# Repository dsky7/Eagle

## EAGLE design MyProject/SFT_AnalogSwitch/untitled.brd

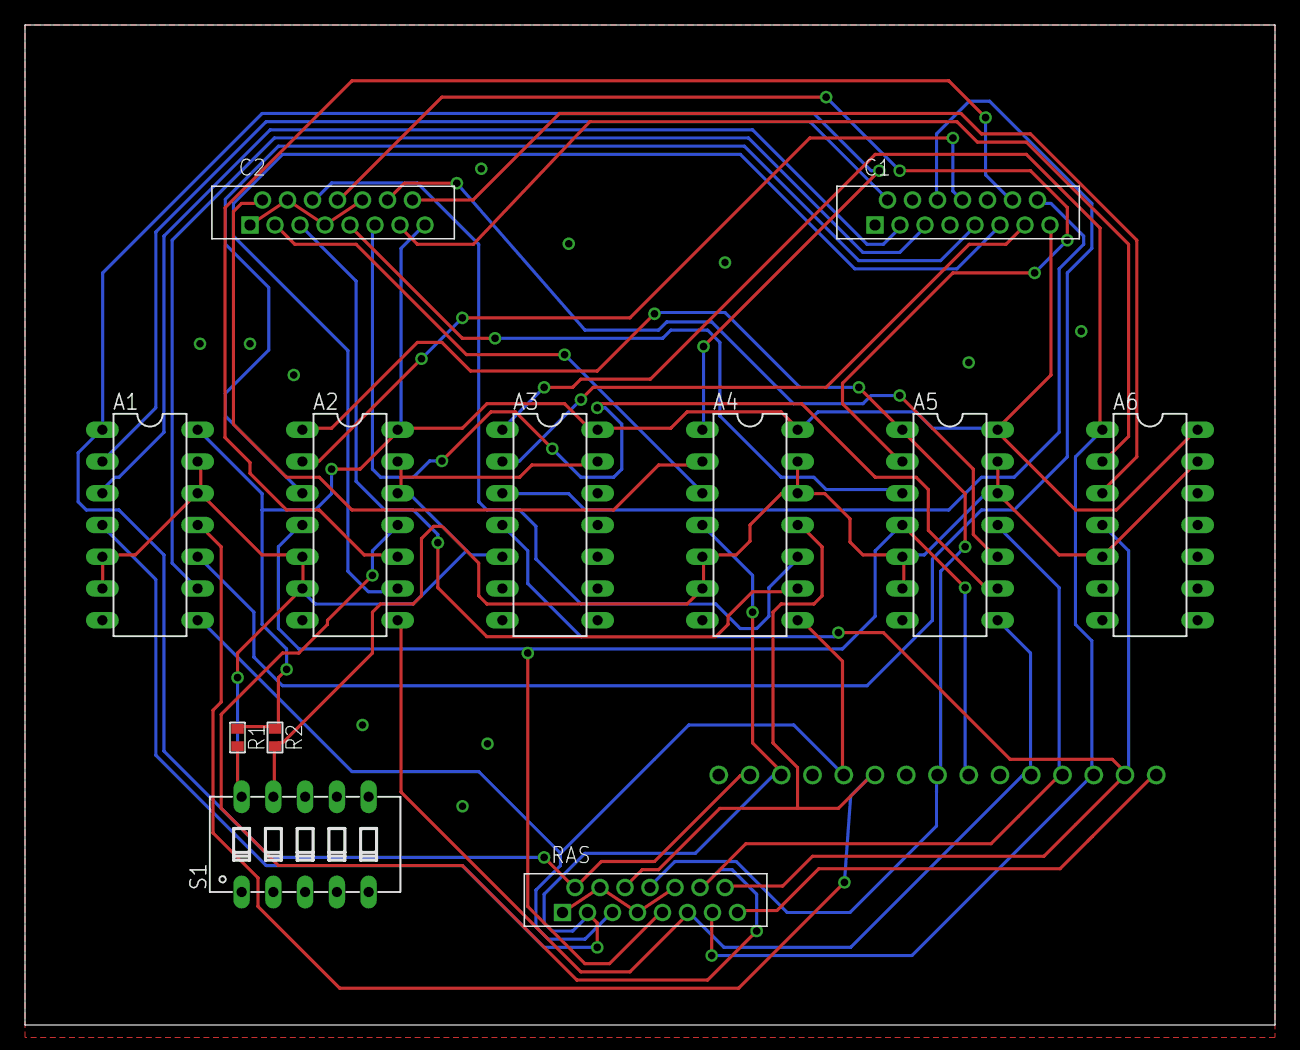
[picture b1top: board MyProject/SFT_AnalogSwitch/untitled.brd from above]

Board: 2 copper layers, 100.0 x 80.0 mm, 27 parts (0 on the bottom side), 35 nets.

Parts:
A1, A2, A3, A4, A5, A6: SN74HC4066; DIL14
C1, C2: FMZ15
R1, R2: 1608
RAS: FMZ15
S1: DIP05YL
U$4, U$5, U$6, U$7, U$8, U$9, U$10, U$11, U$12, U$13, U$14, U$15, U$16, U$17, U$18: CHECK_0.8MM

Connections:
2: A1.1, A4.1, RAS.2, U$5.P$1
3: A1.4, A4.4, RAS.3, U$6.P$1
5: A1.8, A4.8, RAS.5, U$8.P$1
6: A1.11, A4.11, RAS.6, U$9.P$1
8: A2.1, A5.1, RAS.8, U$11.P$1
9: A2.4, A5.4, RAS.9, U$12.P$1
11: A2.8, A5.8, RAS.11, U$14.P$1
12: A2.11, A5.11, RAS.12, U$15.P$1
13: A3.1, A6.1, RAS.13, U$16.P$1
14: A3.4, A6.4, RAS.14, U$17.P$1
15: RAS.15, U$18.P$1
+3.3V: A1.14, A2.14, A3.14, A4.14, A5.14, A6.14, C1.15, C2.15, R1.2, R2.2
GND: A1.7, A2.7, A3.7, A4.7, A5.7, A6.7, C1.1, C1.4, C1.7, C1.10, C2.1, C2.4, C2.7, C2.10, RAS.1, RAS.4, RAS.7, RAS.10, S1.1, S1.2, U$4.P$1, U$7.P$1, U$10.P$1, U$13.P$1
unnamed: A4.2, C2.2
unnamed: A4.3, C2.3
unnamed: A4.9, C2.5
unnamed: A5.3, C2.9
unnamed: A5.2, C2.8
unnamed: A4.10, C2.6
unnamed: A1.2, C1.2
unnamed: A1.3, C1.3
unnamed: A6.3, C2.14
unnamed: A1.9, C1.5
unnamed: A6.2, C2.13
unnamed: A5.10, C2.12
unnamed: A5.9, C2.11
unnamed: A2.3, C1.9
unnamed: A2.2, C1.8
unnamed: A1.10, C1.6
unnamed: A3.3, C1.14
unnamed: A3.2, C1.13
unnamed: A2.10, C1.12
unnamed: A2.9, C1.11
SIGA: A1.5, A1.6, A1.12, A1.13, A2.5, A2.6, A2.12, A2.13, A3.5, A3.13, R1.1, S1.10
SIGB: A4.5, A4.6, A4.12, A4.13, A5.5, A5.6, A5.12, A5.13, A6.5, A6.13, R2.1, S1.9

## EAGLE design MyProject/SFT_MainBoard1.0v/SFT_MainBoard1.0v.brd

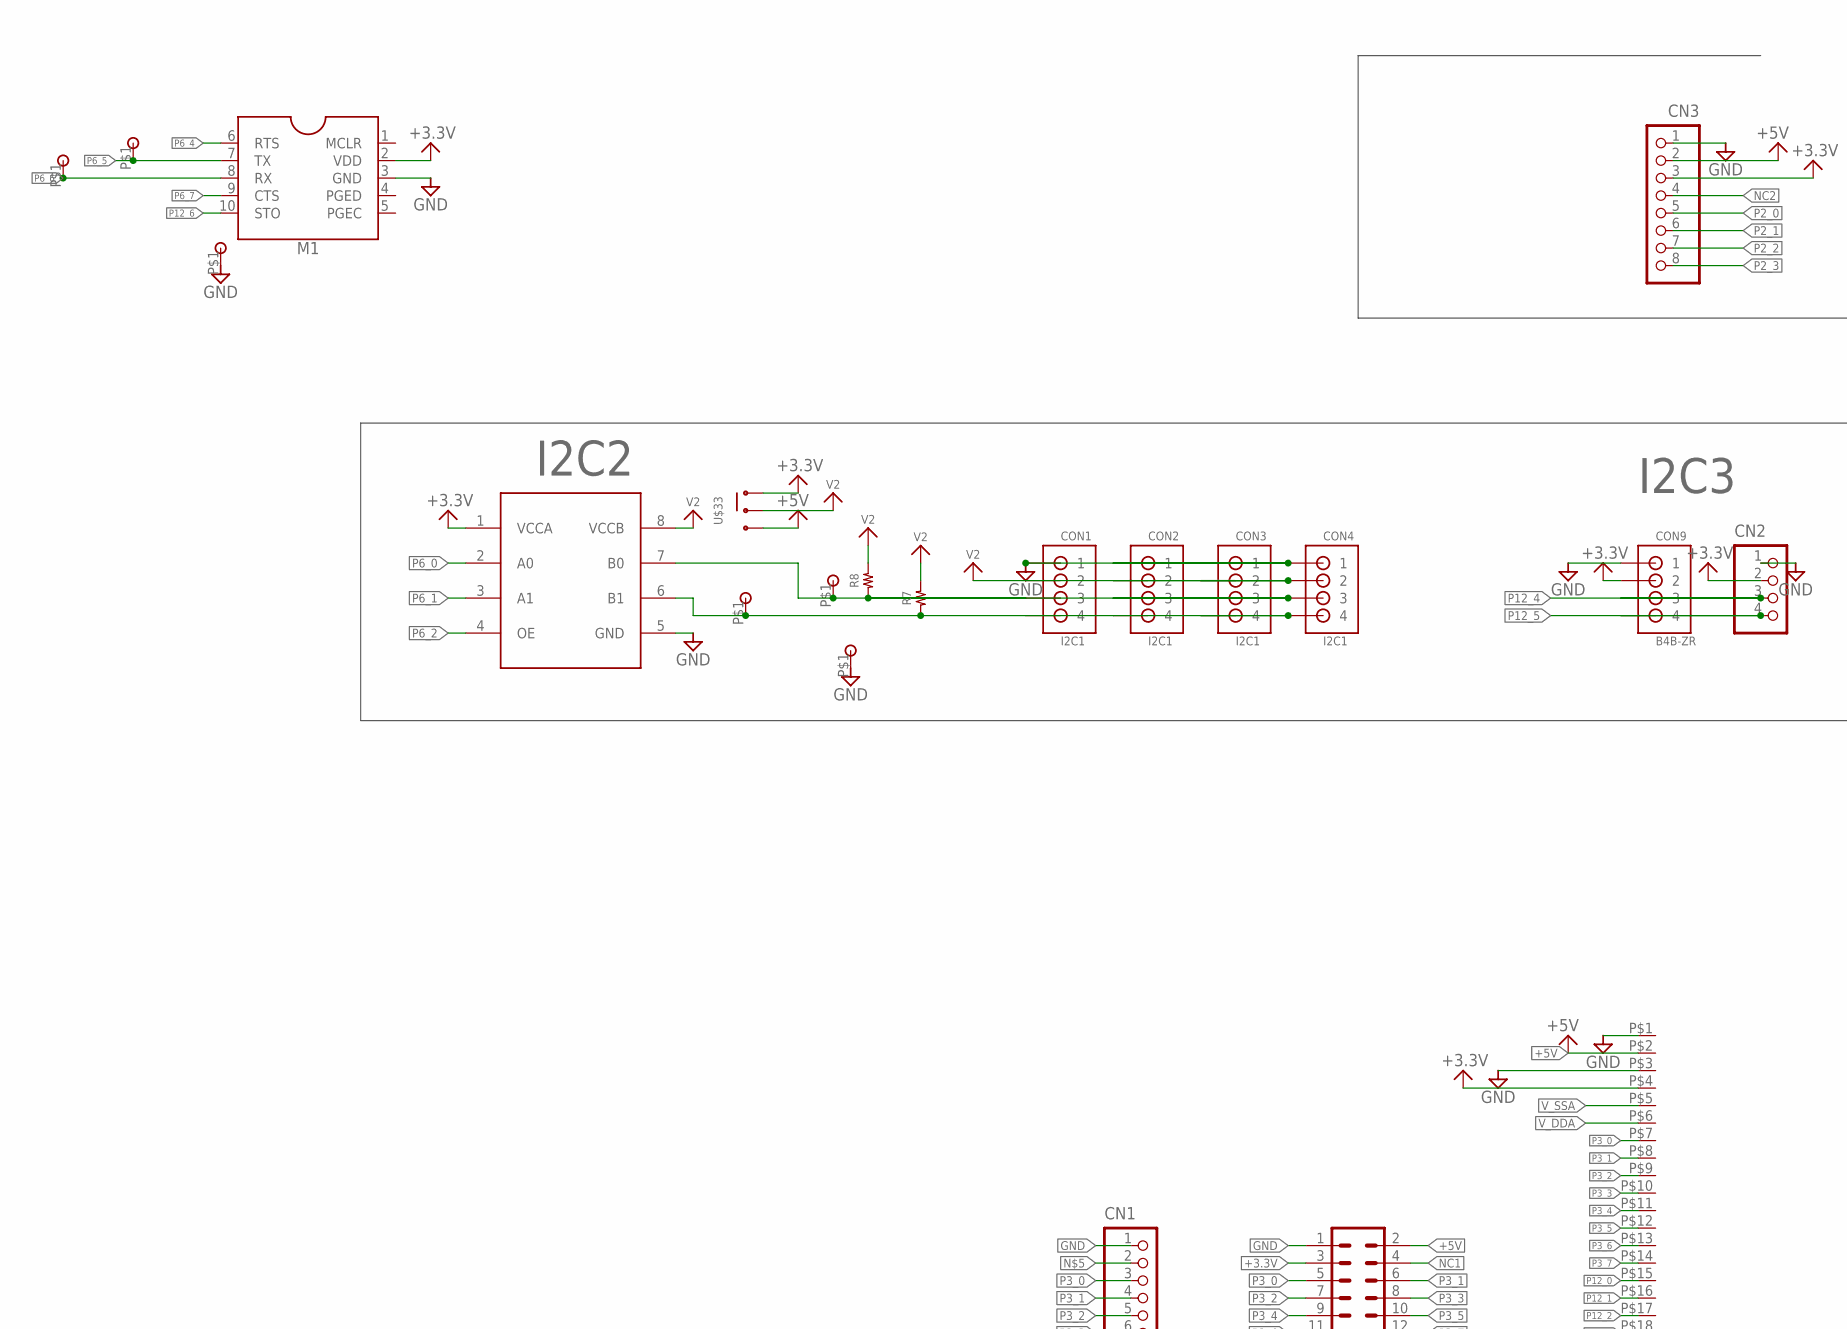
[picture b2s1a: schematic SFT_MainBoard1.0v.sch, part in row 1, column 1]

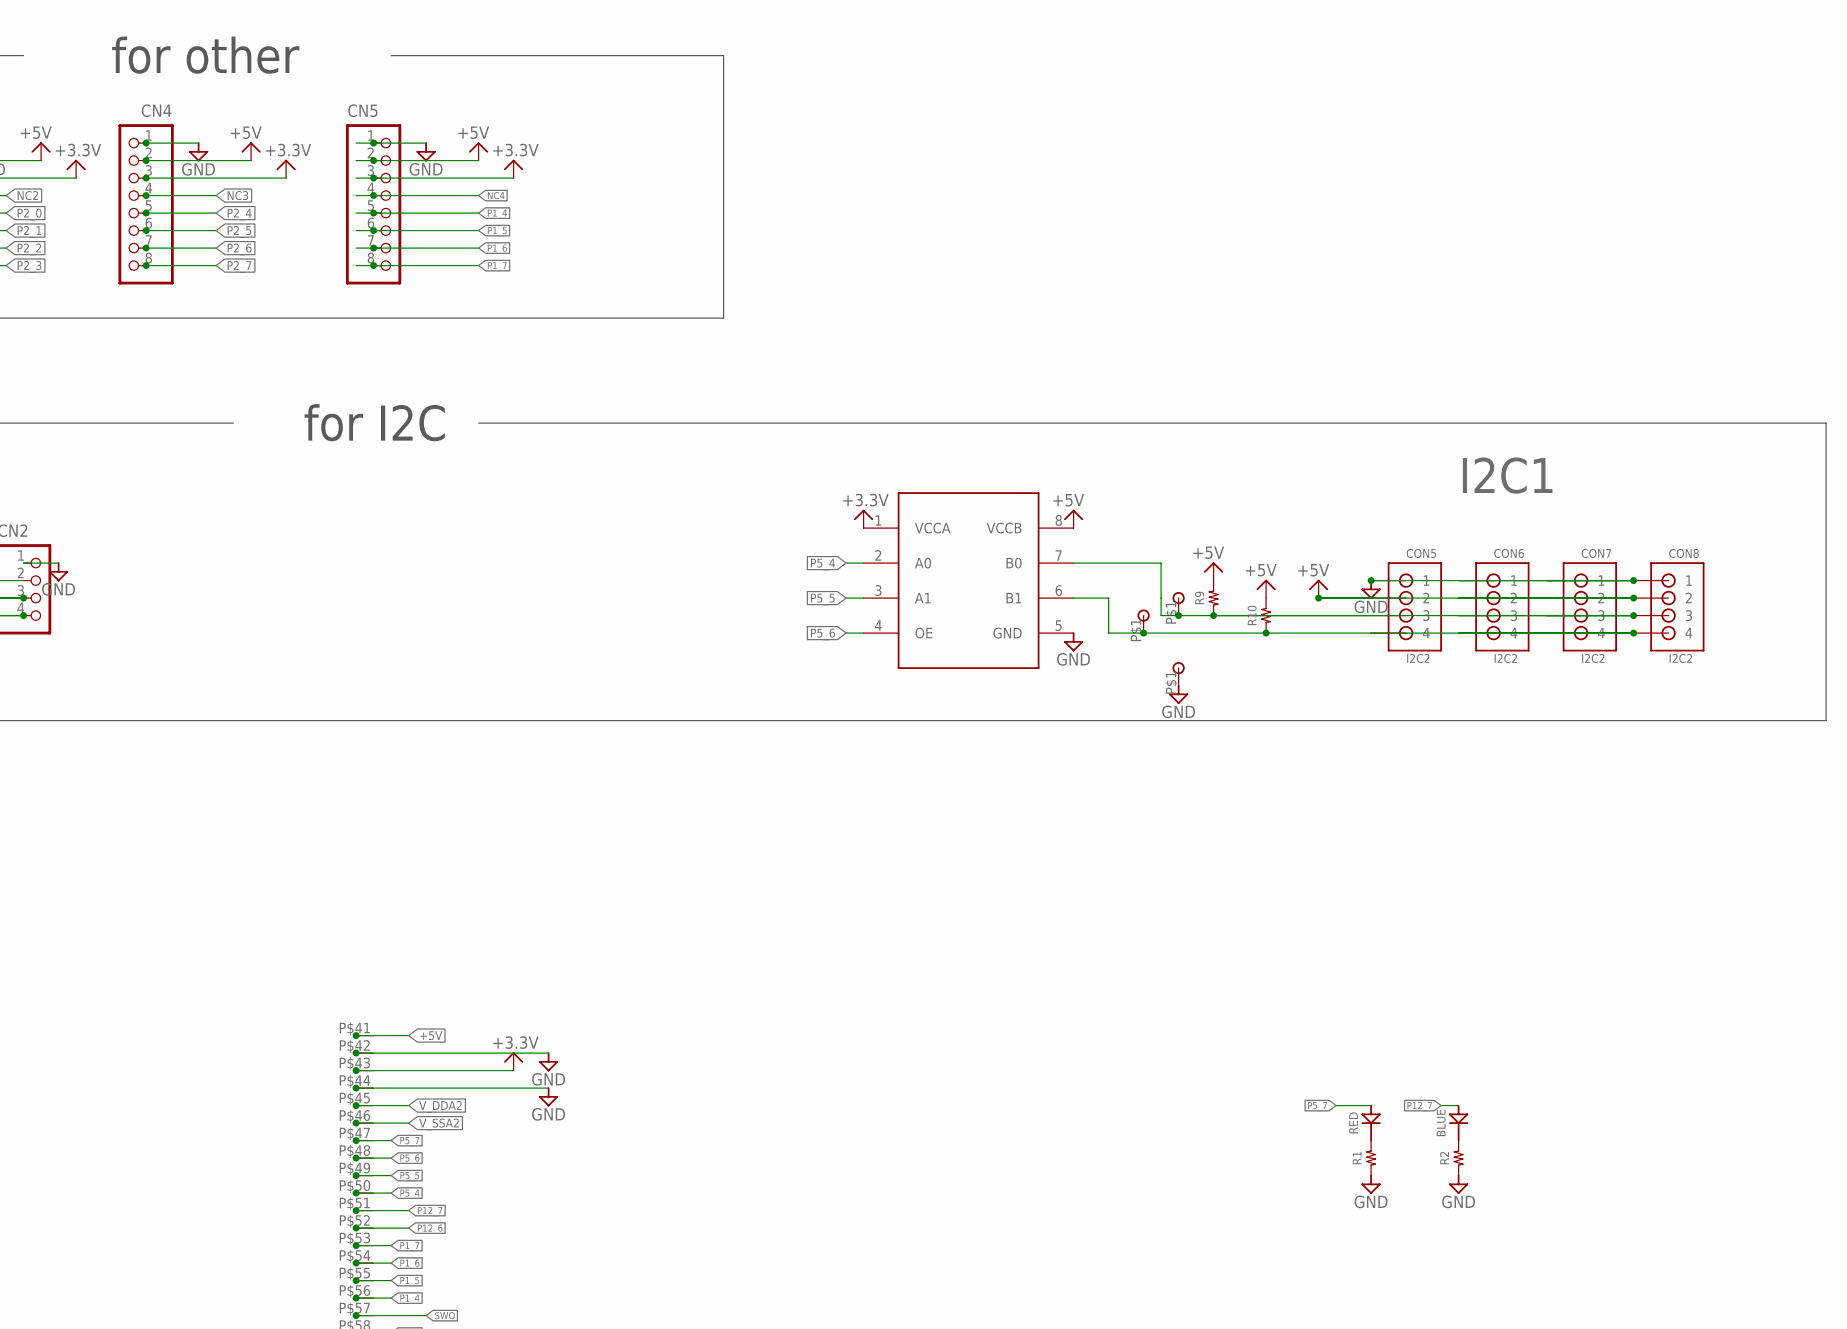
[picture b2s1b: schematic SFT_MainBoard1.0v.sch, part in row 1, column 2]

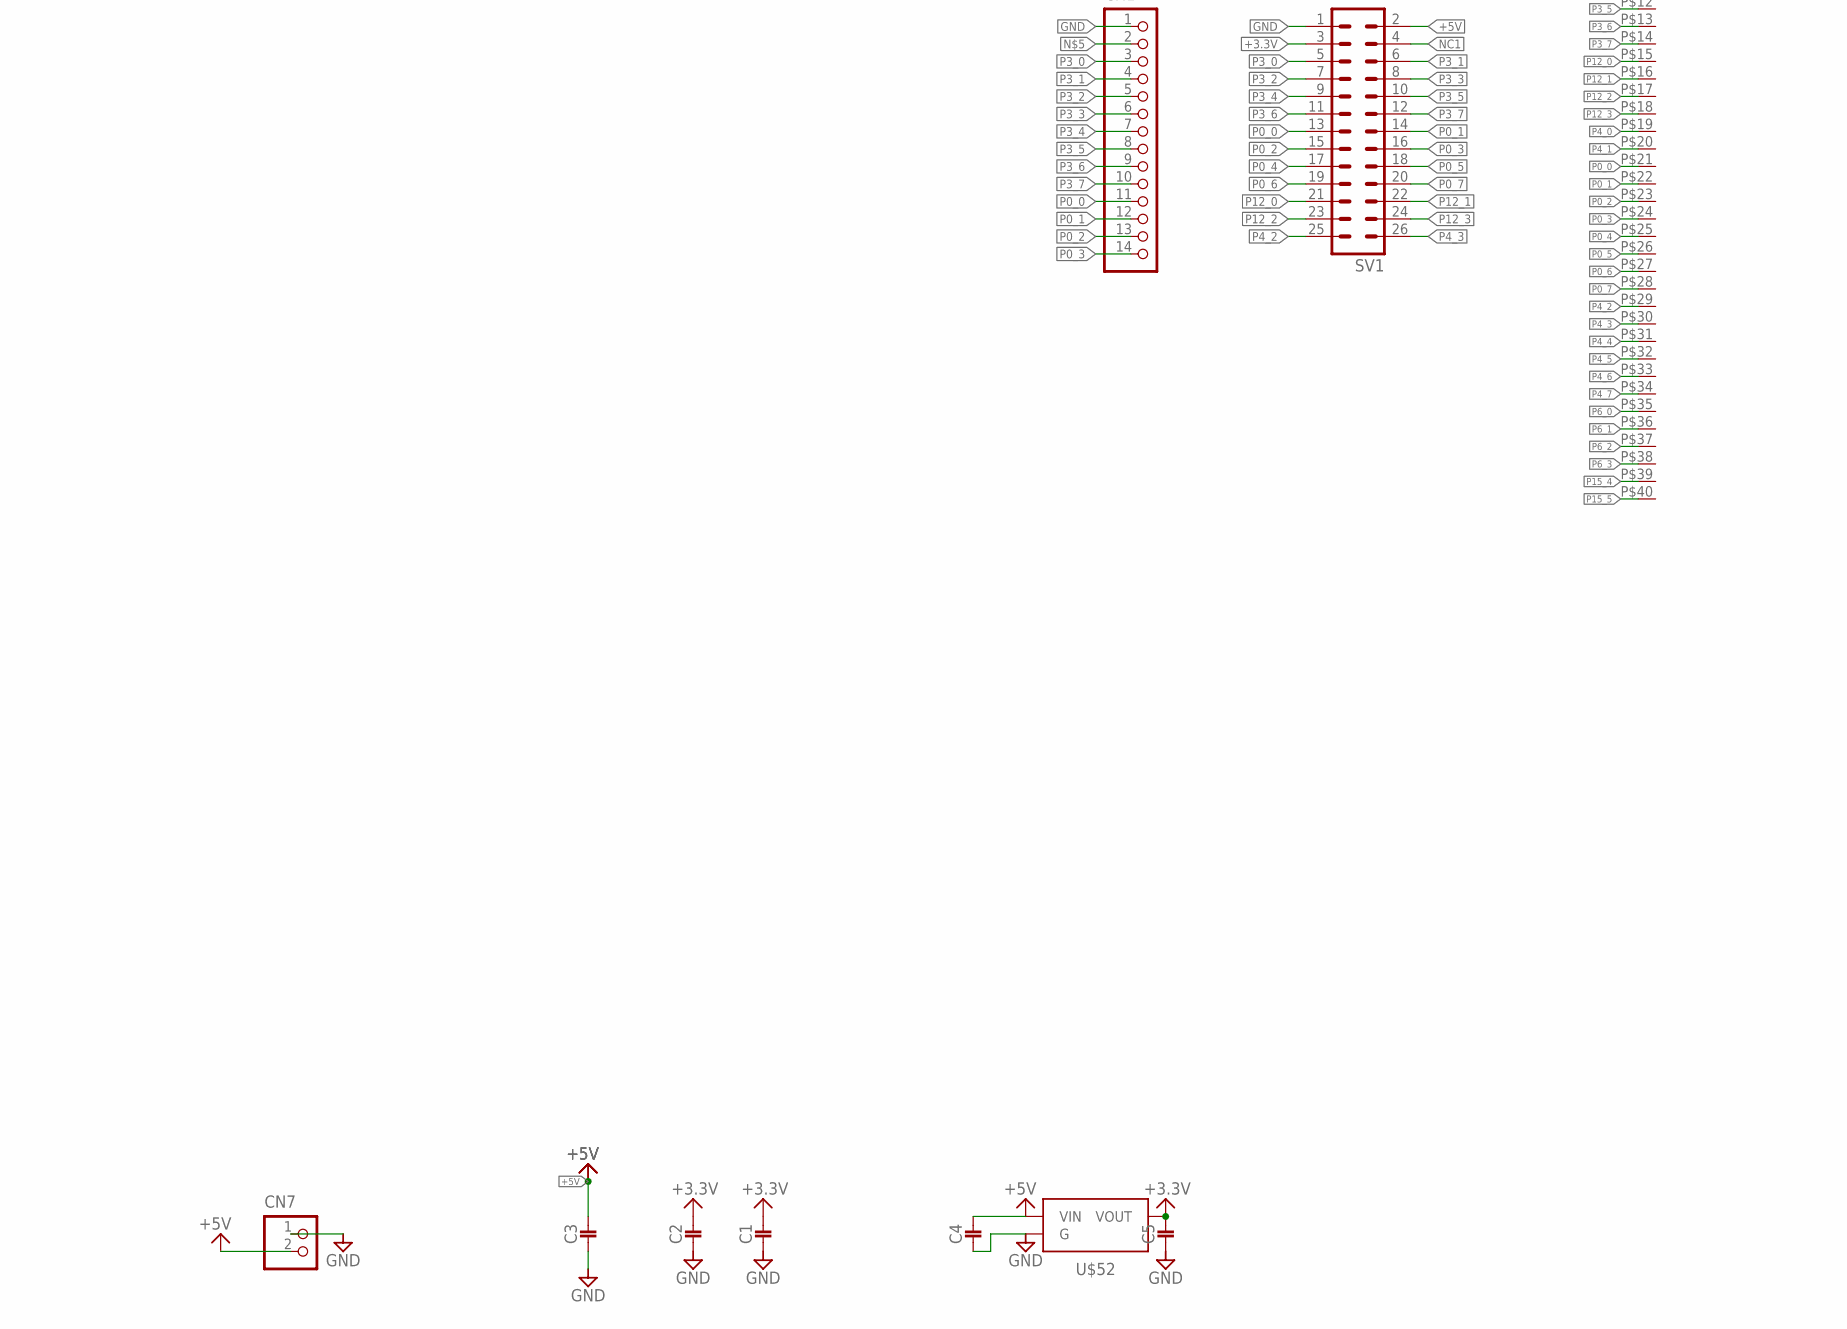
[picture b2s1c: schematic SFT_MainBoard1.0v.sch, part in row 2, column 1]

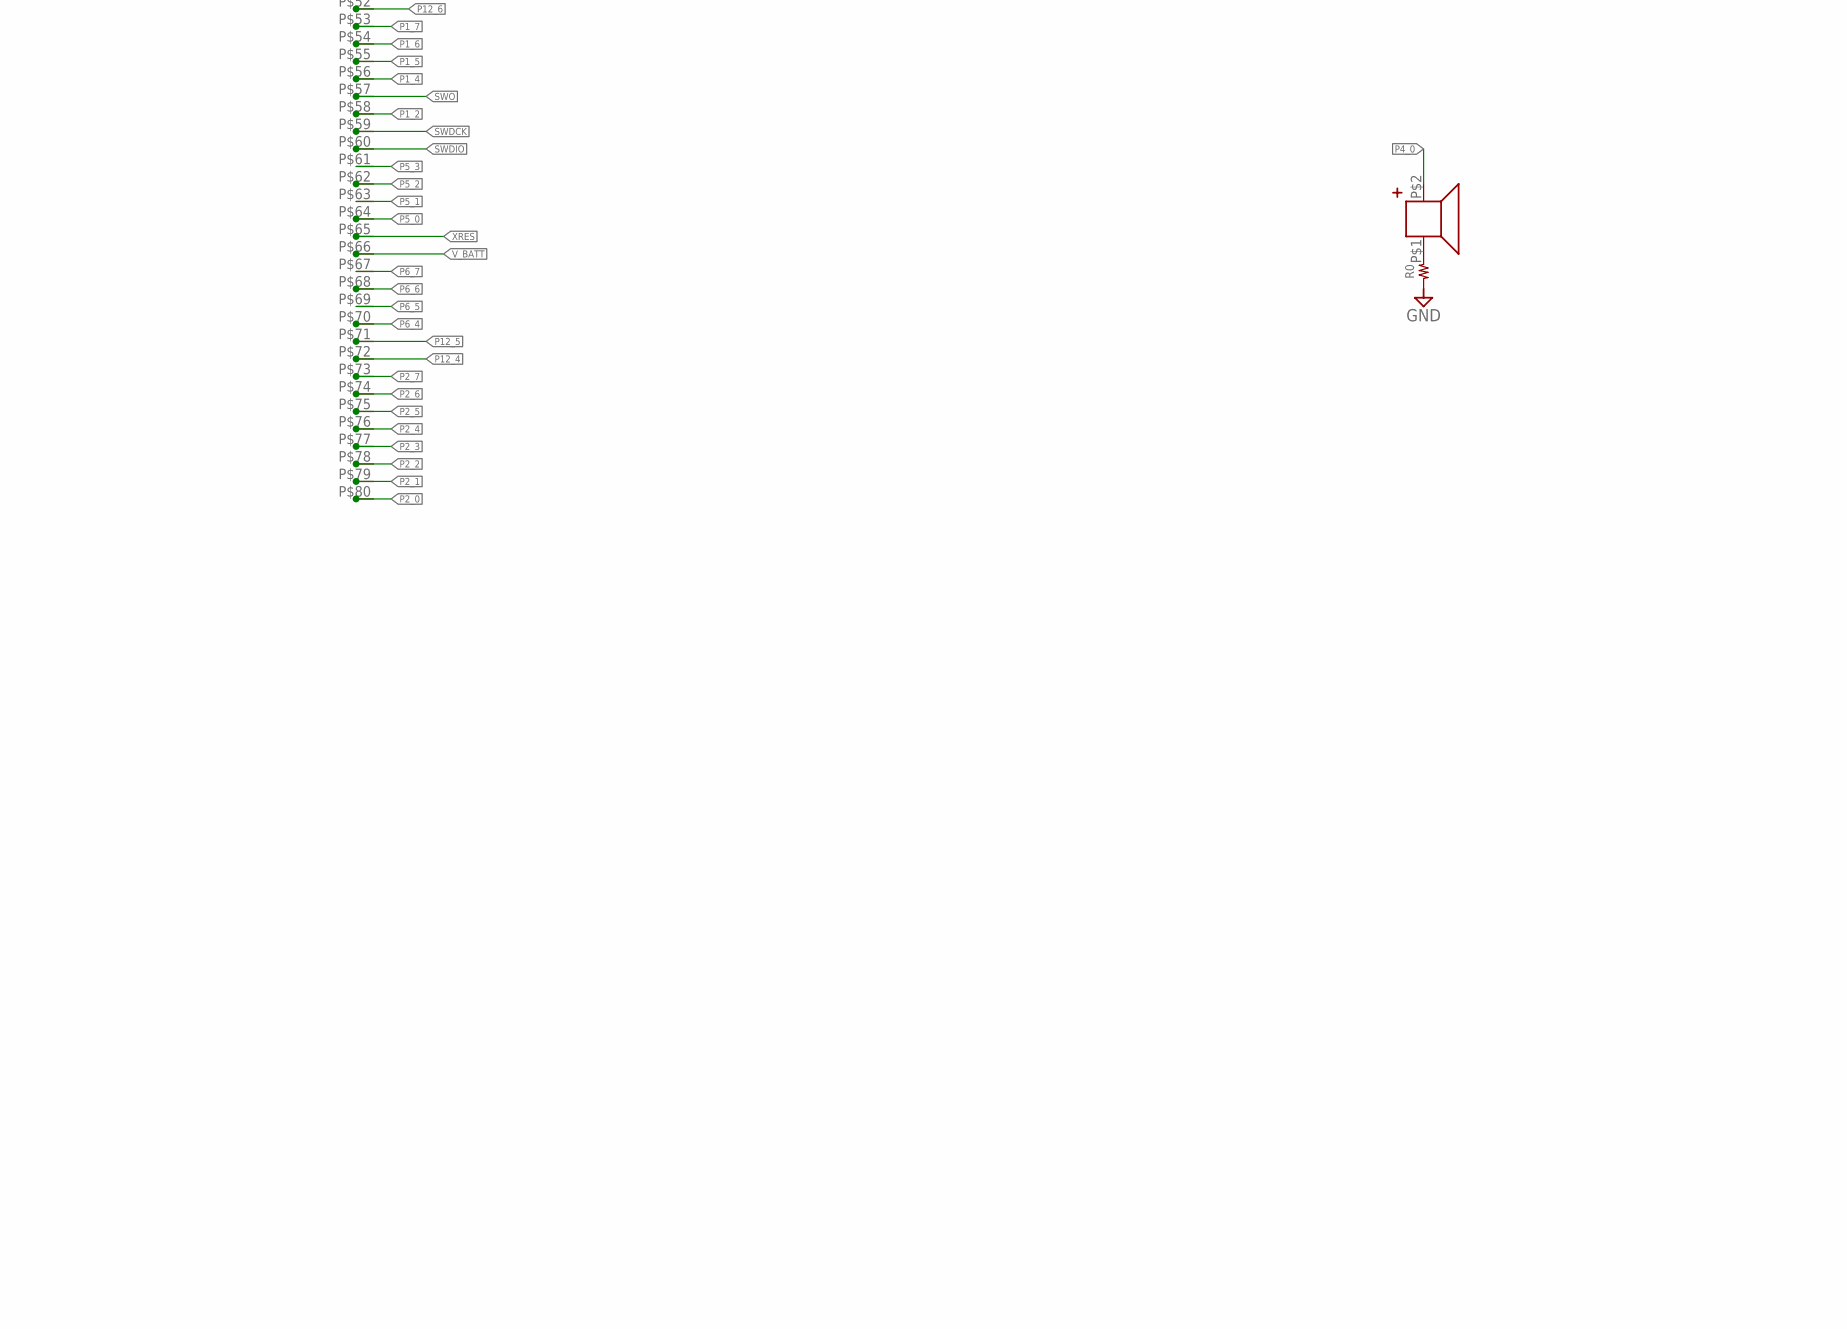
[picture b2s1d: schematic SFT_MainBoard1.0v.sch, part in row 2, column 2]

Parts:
BLUE: CHIPLED; 1608
C1, C2, C3, C4, C5: 1608
CN1: B14B-XASK-1
CN2: B4B-PH-K-S
CN3, CN4, CN5: B8B-PH-K-S
CN7: B2B-PH-K-S
CON1, CON2, CON3, CON4: I2C1; B4B-ZR
CON5, CON6, CON7, CON8: I2C2; B4B-ZR
CON9: B4B-ZR
IC1, IC2: I2C_FXMA2102; DIL08
M1: SBDBT; DIL10
R0, R1, R2, R7, R8, R9, R10: RESISTOR__SMD; 1608
RED: CHIPLED; 1608
SP: PKLCS1212E4001
SV1: ML26
U$2: PSOC_5LP
U$15, U$18, U$37, U$38, U$39, U$78, U$79, U$82, U$83: CHECK_0.8MM
U$33: SS12D01G4
U$52: NJM2845; TO252

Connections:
+3.3V: C1.P$1 (1), C2.P$1 (1), C5.P$1 (1), CN2.2, CN3.3, CN4.3, CN5.3, CON9.2, IC1.1 (VCCA), IC2.1 (VCCA), M1.2 (VDD), SV1.3, U$2.P$4, U$2.P$43, U$33.1, U$52.3 (VOUT)
+5V: C3.P$1 (1), C4.P$1 (1), CN3.2, CN4.2, CN5.2, CN7.2, CON5.2, CON6.2, CON7.2, CON8.2, IC1.8 (VCCB), R9.2, R10.2, SV1.2, U$2.P$2, U$2.P$41, U$33.3, U$52.1 (VIN)
GND: C1.P$2 (2), C2.P$2 (2), C3.P$2 (2), C4.P$2 (2), C5.P$2 (2), CN1.1, CN2.1, CN3.1, CN4.1, CN5.1, CN7.1, CON1.1, CON2.1, CON3.1, CON4.1, CON5.1, CON6.1, CON7.1, CON8.1, CON9.1, IC1.5 (GND), IC2.5 (GND), M1.3 (GND), R0.1, R1.1, R2.1, SV1.1, U$2.P$1, U$2.P$3, U$2.P$42, U$2.P$44, U$37.P$1, U$38.P$1, U$39.P$1, U$52.2 (G)
unnamed: R0.2, SP.P$1 (MINUS)
unnamed: R1.2, RED.2 (K)
unnamed: BLUE.2 (K), R2.2
unnamed: CON1.3, CON2.3, CON3.3, CON4.3, IC2.7 (B0), R8.1, U$79.P$1
unnamed: CON1.4, CON2.4, CON3.4, CON4.4, IC2.6 (B1), R7.1, U$78.P$1
unnamed: CON5.3, CON6.3, CON7.3, CON8.3, IC1.7 (B0), R9.1, U$18.P$1
unnamed: CON5.4, CON6.4, CON7.4, CON8.4, IC1.6 (B1), R10.1, U$15.P$1
NC1: SV1.4
NC2: CN3.4
NC3: CN4.4
NC4: CN5.4
P0_0: CN1.11, SV1.13, U$2.P$21
P0_1: CN1.12, SV1.14, U$2.P$22
P0_2: CN1.13, SV1.15, U$2.P$23
P0_3: CN1.14, SV1.16, U$2.P$24
P0_4: SV1.17, U$2.P$25
P0_5: SV1.18, U$2.P$26
P0_6: SV1.19, U$2.P$27
P0_7: SV1.20, U$2.P$28
P1_2: U$2.P$58
P1_4: CN5.5, U$2.P$56
P1_5: CN5.6, U$2.P$55
P1_6: CN5.7, U$2.P$54
P1_7: CN5.8, U$2.P$53
P2_0: CN3.5, U$2.P$80
P2_1: CN3.6, U$2.P$79
P2_2: CN3.7, U$2.P$78
P2_3: CN3.8, U$2.P$77
P2_4: CN4.5, U$2.P$76
P2_5: CN4.6, U$2.P$75
P2_6: CN4.7, U$2.P$74
P2_7: CN4.8, U$2.P$73
P3_0: CN1.3, SV1.5, U$2.P$7
P3_1: CN1.4, SV1.6, U$2.P$8
P3_2: CN1.5, SV1.7, U$2.P$9
P3_3: CN1.6, SV1.8, U$2.P$10
P3_4: CN1.7, SV1.9, U$2.P$11
P3_5: CN1.8, SV1.10, U$2.P$12
P3_6: CN1.9, SV1.11, U$2.P$13
P3_7: CN1.10, SV1.12, U$2.P$14
P4_0: SP.P$2 (PLUS), U$2.P$19
P4_1: U$2.P$20
P4_2: SV1.25, U$2.P$29
P4_3: SV1.26, U$2.P$30
P4_4: U$2.P$31
P4_5: U$2.P$32
P4_6: U$2.P$33
P4_7: U$2.P$34
P5_0: U$2.P$64
P5_1: U$2.P$63
P5_2: U$2.P$62
P5_3: U$2.P$61
P5_4: IC1.2 (A0), U$2.P$50
P5_5: IC1.3 (A1), U$2.P$49
P5_6: IC1.4 (OE), U$2.P$48
P5_7: RED.1 (A), U$2.P$47
P6_0: IC2.2 (A0), U$2.P$35
P6_1: IC2.3 (A1), U$2.P$36
P6_2: IC2.4 (OE), U$2.P$37
P6_3: U$2.P$38
P6_4: M1.6 (RTS), U$2.P$70
P6_5: M1.7 (TX), U$2.P$69, U$82.P$1
P6_6: M1.8 (RX), U$2.P$68, U$83.P$1
P6_7: M1.9 (CTS), U$2.P$67
P12_0: SV1.21, U$2.P$15
P12_1: SV1.22, U$2.P$16
P12_2: SV1.23, U$2.P$17
P12_3: SV1.24, U$2.P$18
P12_4: CN2.3, CON9.3, U$2.P$72
P12_5: CN2.4, CON9.4, U$2.P$71
P12_6: M1.10 (STO), U$2.P$52
P12_7: BLUE.1 (A), U$2.P$51
P15_4: U$2.P$39
P15_5: U$2.P$40
SWDCK: U$2.P$59
SWDIO: U$2.P$60
SWO: U$2.P$57
V2: CON1.2, CON2.2, CON3.2, CON4.2, IC2.8 (VCCB), R7.2, R8.2, U$33.2
V_BATT: U$2.P$66
V_DDA: U$2.P$6
V_DDA2: U$2.P$45
V_SSA: U$2.P$5
V_SSA2: U$2.P$46
XRES: U$2.P$65

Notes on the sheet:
for I2C
for other
I2C2
I2C1
I2C3

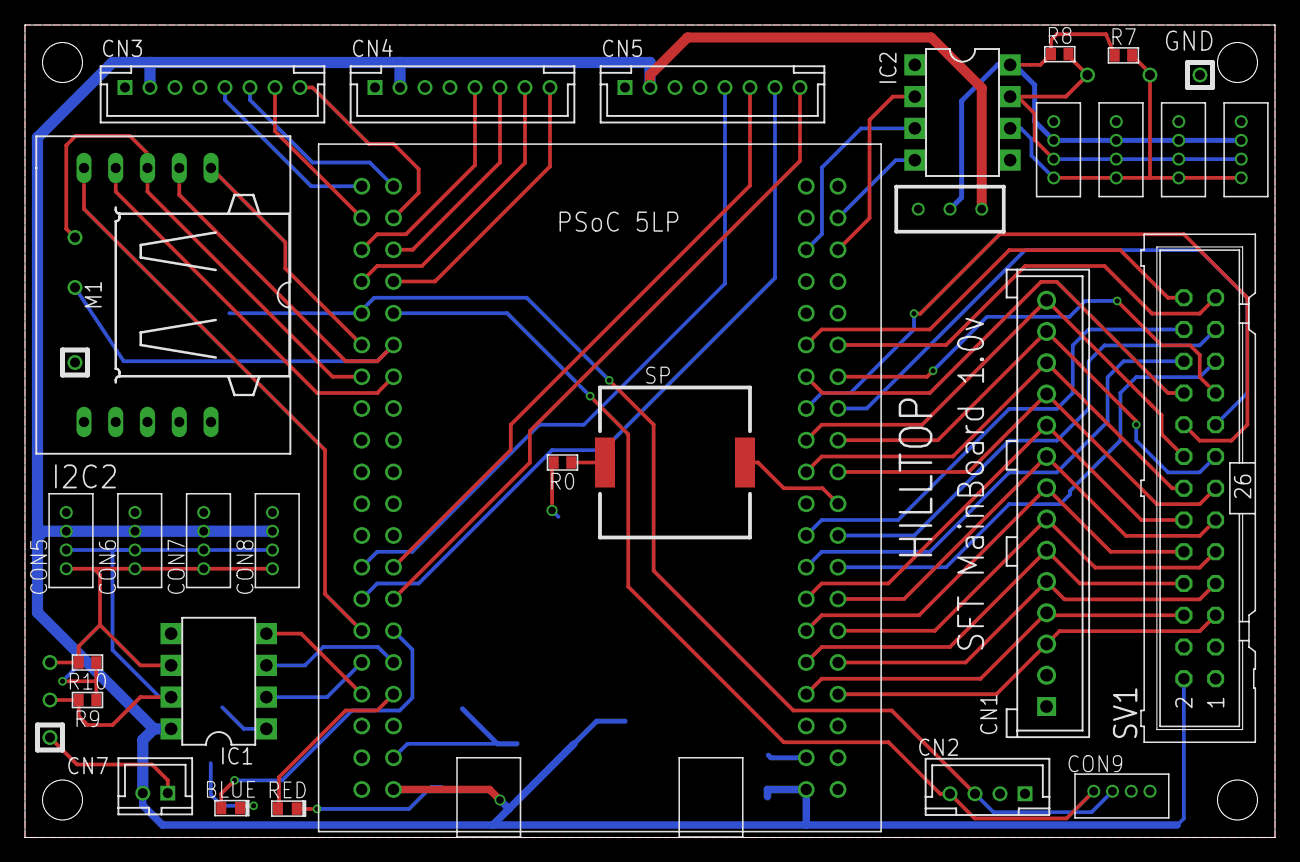
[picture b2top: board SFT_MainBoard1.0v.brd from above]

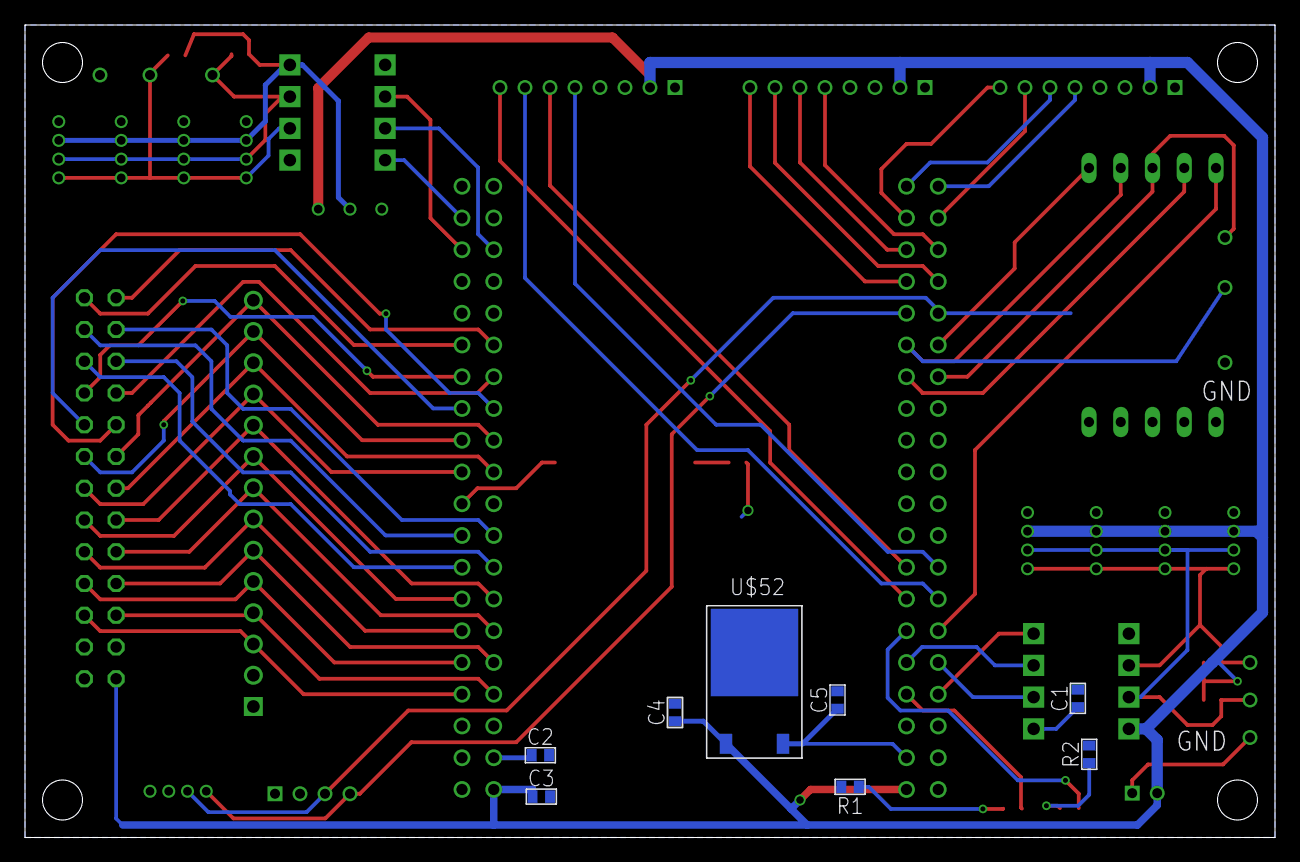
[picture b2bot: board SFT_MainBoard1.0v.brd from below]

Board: 4 copper layers, 100.0 x 65.0 mm, 47 parts (8 on the bottom side), 61 nets.

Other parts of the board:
DRILEGEND: DRILEGEND

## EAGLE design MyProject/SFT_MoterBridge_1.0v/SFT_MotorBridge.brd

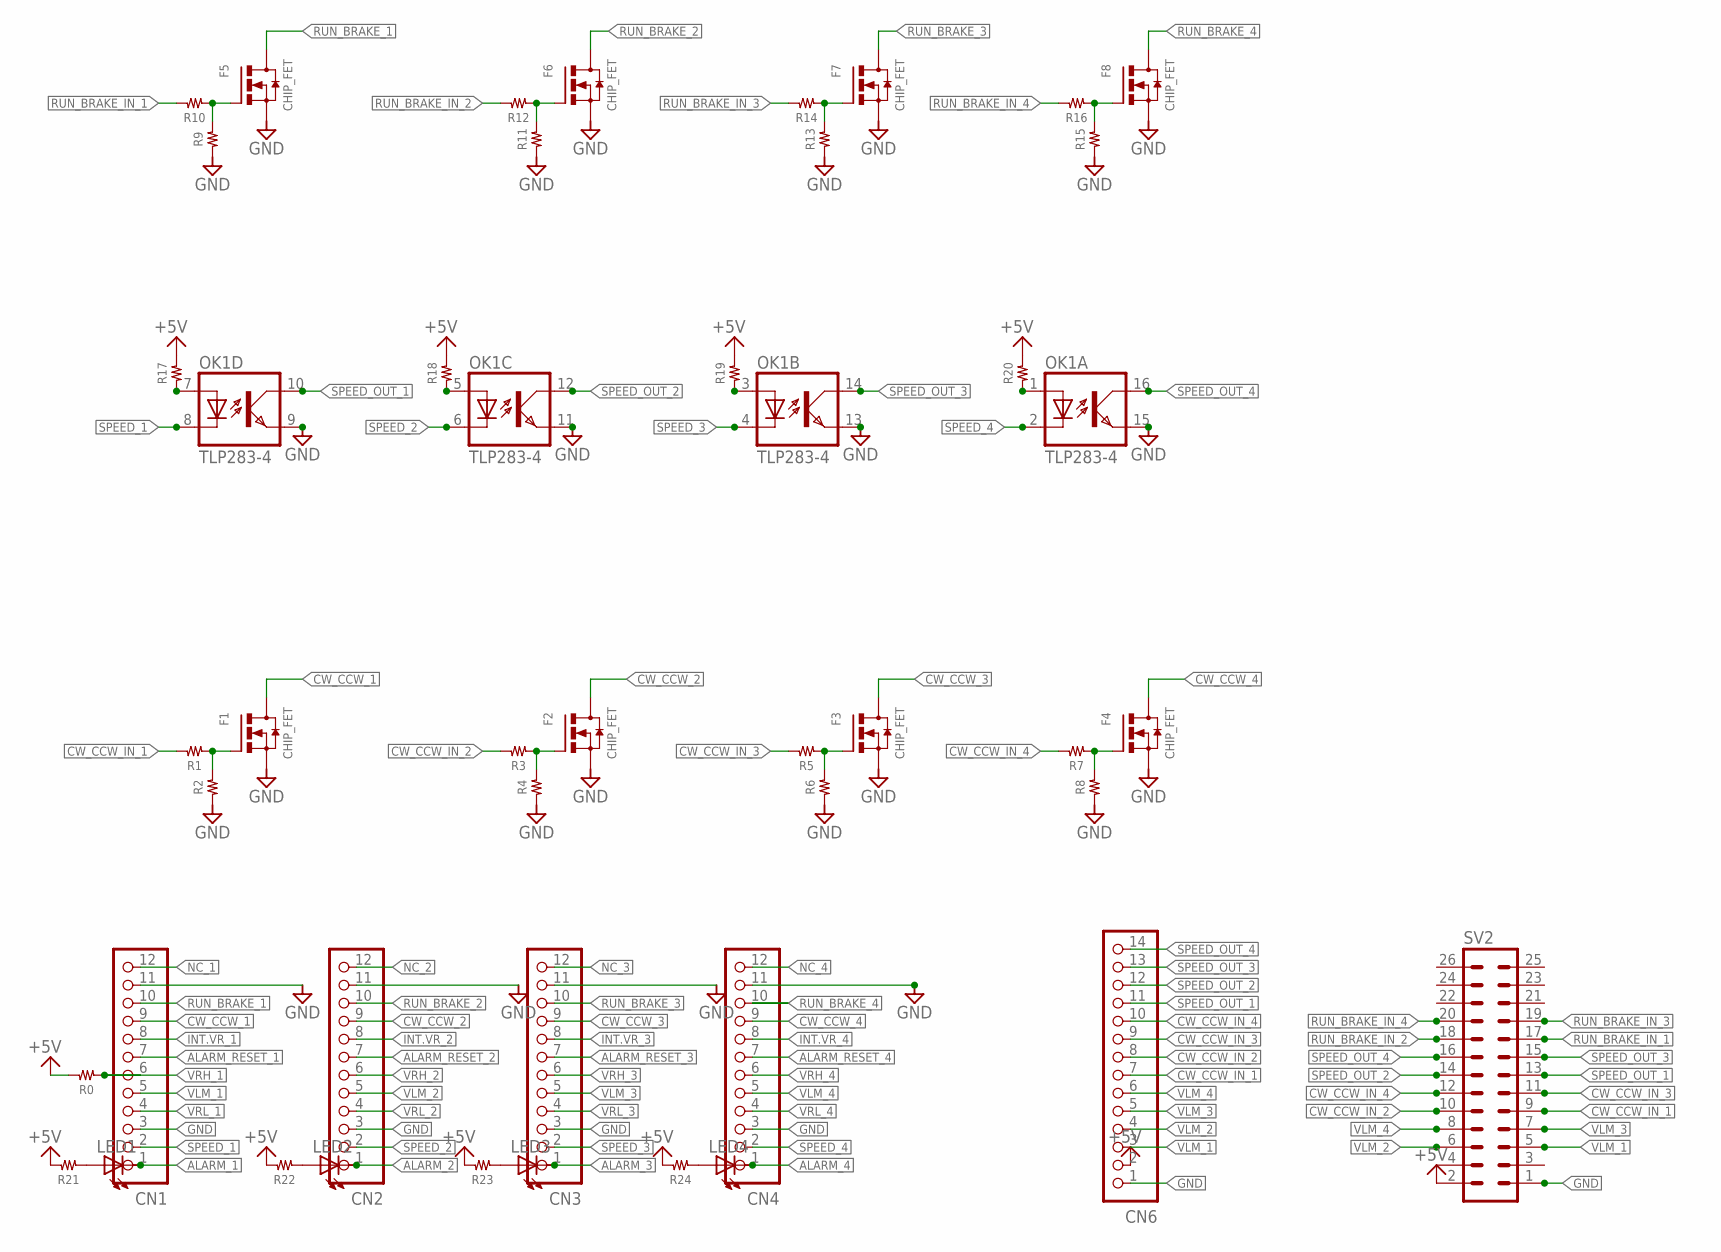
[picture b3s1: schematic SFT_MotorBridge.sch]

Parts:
CN1, CN2, CN3, CN4: B12B-XASK-1
CN6: B14B-XASK-1
F1, F2, F3, F4, F5, F6, F7, F8: CHIP_FET; SOT23
LED1, LED2, LED3, LED4: LED5MM
OK1: TLP283-4; MINI-FLAT-16
R0, R1, R2, R3, R4, R5, R6, R7, R8, R9, R10, R11, R12, R13, R14, R15, R16, R17, R18, R19, R20, R21, R22, R23, R24: RESISTOR__SMD; 1608
SV2: ML26

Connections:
+5V: CN6.2, R0.2, R17.2, R18.2, R19.2, R20.2, R21.2, R22.2, R23.2, R24.2, SV2.2
ALARM_1: CN1.1, LED1.K (C)
ALARM_2: CN2.1, LED2.K (C)
ALARM_3: CN3.1, LED3.K (C)
ALARM_4: CN4.1, LED4.K (C)
ALARM_RESET_1: CN1.7
ALARM_RESET_2: CN2.7
ALARM_RESET_3: CN3.7
ALARM_RESET_4: CN4.7
CW_CCW_1: CN1.9, F1.3 (D)
CW_CCW_2: CN2.9, F2.3 (D)
CW_CCW_3: CN3.9, F3.3 (D)
CW_CCW_4: CN4.9, F4.3 (D)
CW_CCW_IN_1: CN6.7, R1.2, SV2.9
CW_CCW_IN_2: CN6.8, R3.2, SV2.10
CW_CCW_IN_3: CN6.9, R5.2, SV2.11
CW_CCW_IN_4: CN6.10, R7.2, SV2.12
GND: CN1.3, CN1.11, CN2.3, CN2.11, CN3.3, CN3.11, CN4.3, CN4.11, F1.2 (S), F2.2 (S), F3.2 (S), F4.2 (S), F5.2 (S), F6.2 (S), F7.2 (S), F8.2 (S), OK1.9 (EMIT), OK1.11 (EMIT), OK1.13 (EMIT), OK1.15 (EMIT), R2.1, R4.1, R6.1, R8.1, R9.1, R11.1, R13.1, R15.1, SV2.1
INT.VR_1: CN1.8
INT.VR_2: CN2.8
INT.VR_3: CN3.8
INT.VR_4: CN4.8
unnamed: F1.1 (G), R1.1, R2.2
unnamed: F2.1 (G), R3.1, R4.2
unnamed: F3.1 (G), R5.1, R6.2
unnamed: F4.1 (G), R7.1, R8.2
unnamed: OK1.3 (A), R19.1
unnamed: OK1.5 (A), R18.1
unnamed: OK1.7 (A), R17.1
unnamed: OK1.1 (A), R20.1
unnamed: F5.1 (G), R9.2, R10.1
unnamed: F6.1 (G), R11.2, R12.1
unnamed: F7.1 (G), R13.2, R14.1
unnamed: F8.1 (G), R15.2, R16.1
unnamed: LED1.A, R21.1
unnamed: LED2.A, R22.1
unnamed: LED3.A, R23.1
unnamed: LED4.A, R24.1
NC_1: CN1.12
NC_2: CN2.12
NC_3: CN3.12
NC_4: CN4.12
RUN_BRAKE_1: CN1.10, F5.3 (D)
RUN_BRAKE_2: CN2.10, F6.3 (D)
RUN_BRAKE_3: CN3.10, F7.3 (D)
RUN_BRAKE_4: CN4.10, F8.3 (D)
RUN_BRAKE_IN_1: R10.2, SV2.17
RUN_BRAKE_IN_2: R12.2, SV2.18
RUN_BRAKE_IN_3: R14.2, SV2.19
RUN_BRAKE_IN_4: R16.2, SV2.20
SPEED_1: CN1.2, OK1.8 (C)
SPEED_2: CN2.2, OK1.6 (C)
SPEED_3: CN3.2, OK1.4 (C)
SPEED_4: CN4.2, OK1.2 (C)
SPEED_OUT_1: CN6.11, OK1.10 (COL), SV2.13
SPEED_OUT_2: CN6.12, OK1.12 (COL), SV2.14
SPEED_OUT_3: CN6.13, OK1.14 (COL), SV2.15
SPEED_OUT_4: CN6.14, OK1.16 (COL), SV2.16
VLM_1: CN1.5, CN6.3, SV2.5
VLM_2: CN2.5, CN6.4, SV2.6
VLM_3: CN3.5, CN6.5, SV2.7
VLM_4: CN4.5, CN6.6, SV2.8
VRH_1: CN1.6, R0.1
VRH_2: CN2.6
VRH_3: CN3.6
VRH_4: CN4.6
VRL_1: CN1.4
VRL_2: CN2.4
VRL_3: CN3.4
VRL_4: CN4.4

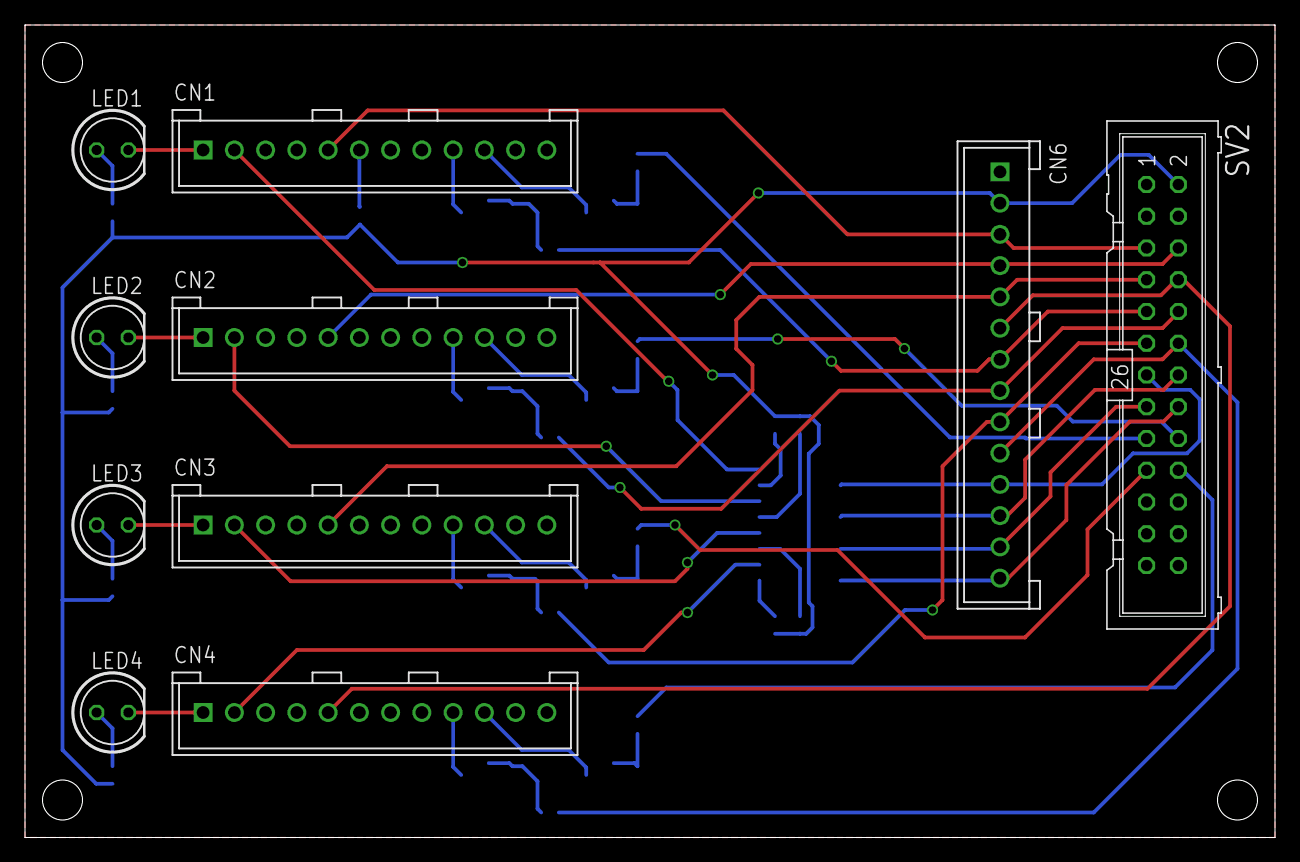
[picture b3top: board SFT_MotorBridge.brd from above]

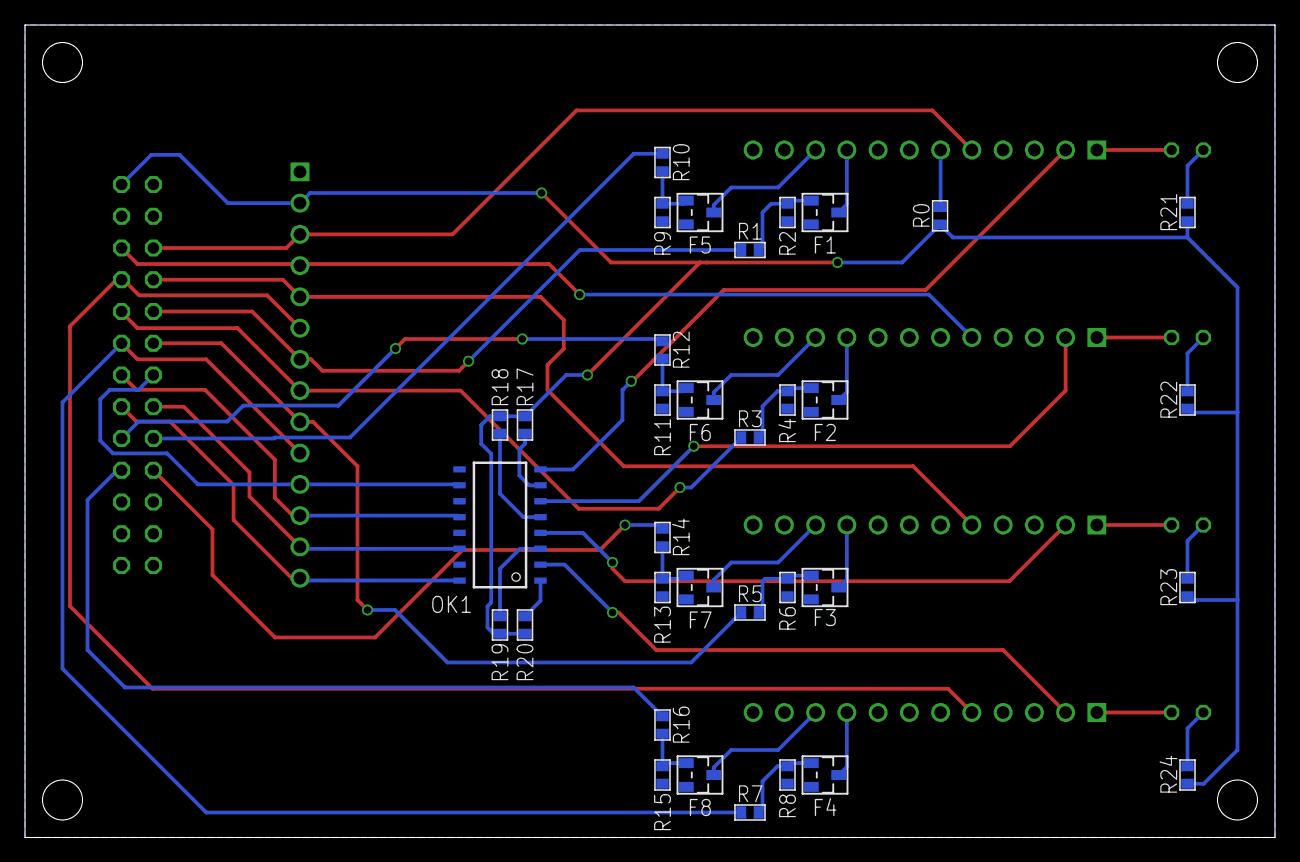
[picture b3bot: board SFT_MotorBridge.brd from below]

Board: 4 copper layers, 100.0 x 65.0 mm, 45 parts (34 on the bottom side), 51 nets.

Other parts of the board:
DRILEGEND: DRILEGEND
